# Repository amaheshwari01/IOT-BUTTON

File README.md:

# IOT-BUTTON

esp 32 c3 bassed iot buttons

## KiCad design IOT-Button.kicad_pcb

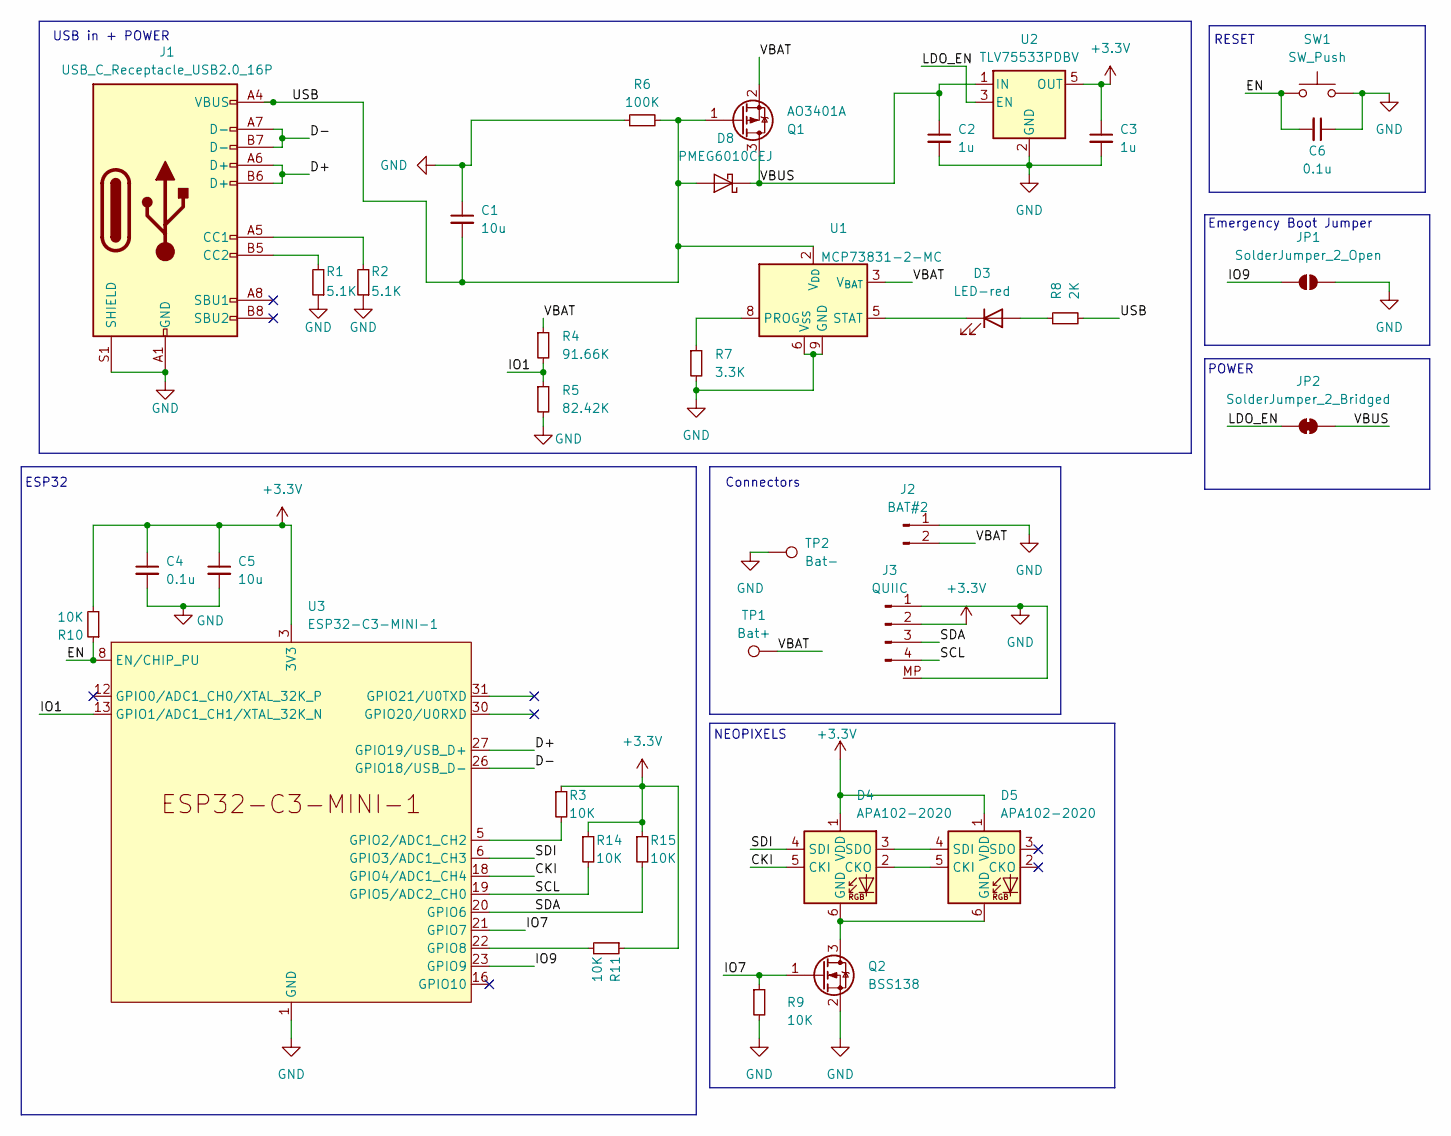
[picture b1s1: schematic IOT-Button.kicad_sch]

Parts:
C1, C5: 10u; C_0603_1608Metric
C2, C3: 1u; C_0603_1608Metric
C4, C6: 0.1u; C_0603_1608Metric
D3: LED-red; LED_0603_1608Metric
D4, D5: APA102-2020; LED-APA102-2020
D8: PMEG6010CEJ; D_SOD-323F
J1: USB_C_Receptacle_USB2.0_16P; USB_C_Receptacle_HRO_TYPE-C-31-M-12
J2: BAT#2; PinHeader_1x02_P1.00mm_Vertical
J3: QUIIC; JST_SH_SM04B-SRSS-TB_1x04-1MP_P1.00mm_Horizontal
JP1: SolderJumper_2_Open; SolderJumper-2_P1.3mm_Open_RoundedPad1.0x1.5mm
JP2: SolderJumper_2_Bridged; SolderJumper-2_P1.3mm_Open_RoundedPad1.0x1.5mm
Q1: AO3401A; SOT-23
Q2: BSS138; SOT-23
R1, R2: 5.1K; R_0603_1608Metric
R3, R9, R10, R11, R14, R15: 10K; R_0603_1608Metric
R4: 91.66K; R_0603_1608Metric
R5: 82.42K; R_0603_1608Metric
R6: 100K; R_0603_1608Metric
R7: 3.3K; R_0603_1608Metric
R8: 2K; R_0603_1608Metric
SW1: SW_Push; SW_Push_1P1T_NO_CK_PTS125Sx43PSMTR
TP1: Bat+; TestPoint_Pad_2.5x2.5mm
TP2: Bat-; TestPoint_Pad_2.5x2.5mm
U1: MCP73831-2-MC; DFN-8-1EP_3x2mm_P0.5mm_EP1.7x1.4mm
U2: TLV75533PDBV; SOT-23-5
U3: ESP32-C3-MINI-1

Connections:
+3.3V: C3.1, C4.1, C5.1, D4.1 (VDD), D5.1 (VDD), J3.2, R3.1, R10.2, R11.1, R14.1, R15.1, U2.5 (OUT), U3.3 (3V3)
/CKI: D4.5 (CKI), U3.18 (GPIO4/ADC1_CH4)
/D+: J1.A6 (D+), J1.B6 (D+), U3.27 (GPIO19/USB_D+)
/D-: J1.A7 (D-), J1.B7 (D-), U3.26 (GPIO18/USB_D-)
/EN: C6.2, R10.1, SW1.1, U3.8 (EN/CHIP_PU)
/IO1: R4.2, R5.1, U3.13 (GPIO1/ADC1_CH1/XTAL_32K_N)
/IO7: Q2.1 (G), R9.1, U3.21 (GPIO7)
/IO9: JP1.1 (A), U3.23 (GPIO9)
/LDO_EN: JP2.1 (A), U2.3 (EN)
/SCL: J3.4, R14.2, U3.19 (GPIO5/ADC2_CH0)
/SDA: J3.3, R15.2, U3.20 (GPIO6)
/SDI: D4.4 (SDI), U3.6 (GPIO3/ADC1_CH3)
/USB: C1.2, D8.2 (A), J1.A4 (VBUS), J1.A9 (VBUS), J1.B4 (VBUS), J1.B9 (VBUS), Q1.1 (G), R6.2, R8.2, U1.1 (V_{DD}), U1.2 (V_{DD})
/VBAT: J2.2, Q1.2 (S), R4.1, TP1.1, U1.3 (V_{BAT}), U1.4 (V_{BAT})
/VBUS: C2.1, D8.1 (K), JP2.2 (B), Q1.3 (D), U2.1 (IN)
GND: C1.1, C2.2, C3.2, C4.2, C5.2, C6.1, J1.A1 (GND), J1.A12 (GND), J1.B1 (GND), J1.B12 (GND), J1.S1 (SHIELD), J2.1, J3.1, J3.MP, JP1.2 (B), Q2.2 (S), R1.1, R2.1, R5.2, R6.1, R7.2, R9.2, SW1.2, TP2.1, U1.6 (V_{SS}), U1.9 (GND), U2.2 (GND), U3.1 (GND), U3.2 (GND), U3.11 (GND), U3.14 (GND), U3.36 (GND), U3.37 (GND), U3.38 (GND), U3.39 (GND), U3.40 (GND), U3.41 (GND), U3.42 (GND), U3.43 (GND), U3.44 (GND), U3.45 (GND), U3.46 (GND), U3.47 (GND), U3.48 (GND), U3.49 (GND), U3.50 (GND), U3.51 (GND), U3.52 (GND), U3.53 (GND)
unnamed: D3.2 (A), R8.1
unnamed: D3.1 (K), U1.5 (STAT)
unnamed: D4.2 (CKO), D5.5 (CKI)
unnamed: D4.6 (GND), D5.6 (GND), Q2.3 (D)
unnamed: D4.3 (SDO), D5.4 (SDI)
unnamed: J1.A5 (CC1), R2.2
unnamed: J1.B5 (CC2), R1.2
unnamed: R7.1, U1.8 (PROG)
unnamed: R3.2, U3.5 (GPIO2/ADC1_CH2)
unnamed: R11.2, U3.22 (GPIO8)

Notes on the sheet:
ESP32
POWER
NEOPIXELS
USB in + POWER
RESET
Connectors
Emergency Boot Jumper

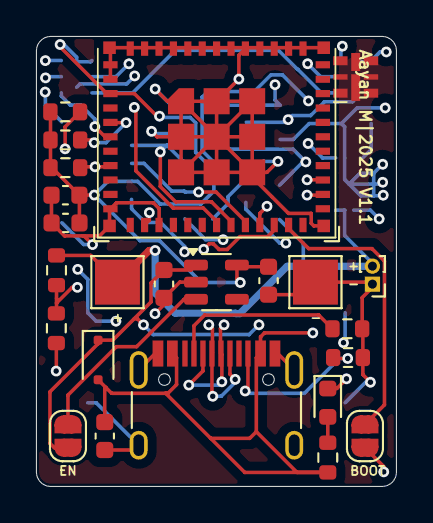
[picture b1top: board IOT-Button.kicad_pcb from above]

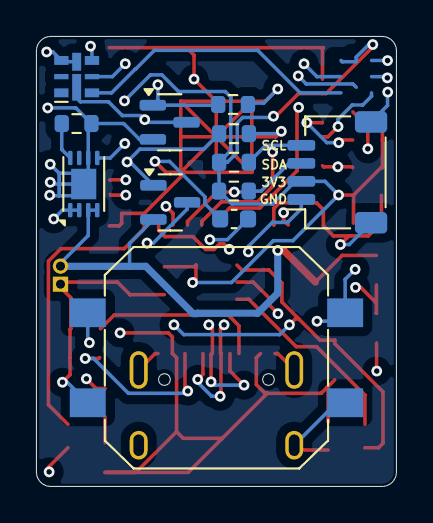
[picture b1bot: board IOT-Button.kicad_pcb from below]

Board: 4 copper layers, 20.0 x 25.0 mm, 36 parts (12 on the bottom side), 26 nets.
